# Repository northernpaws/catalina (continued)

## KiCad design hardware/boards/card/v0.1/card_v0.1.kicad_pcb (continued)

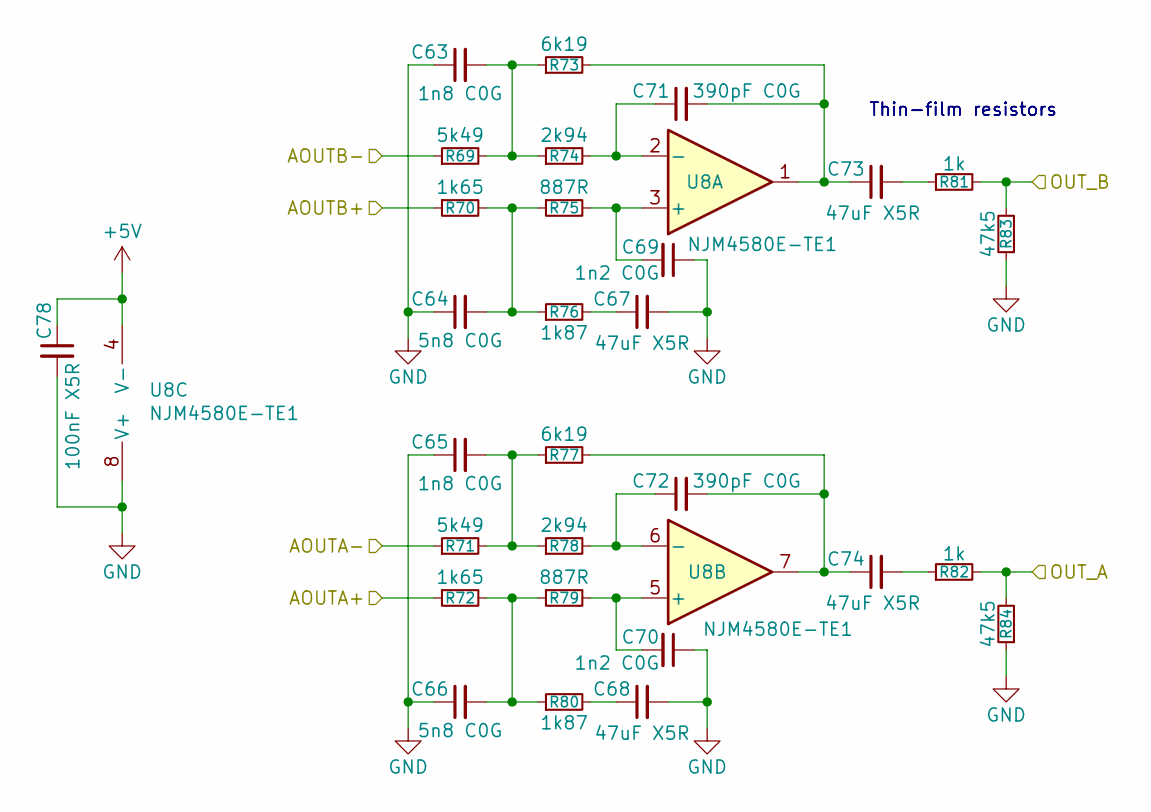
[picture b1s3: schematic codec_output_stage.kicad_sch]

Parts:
C63, C65: 1n8 C0G; C0402
C64, C66: 5n8 C0G; C0402
C67, C68, C73, C74: 47uF X5R; C0805
C69, C70: 1n2 C0G; C0402
C71, C72: 390pF C0G; C0402
C78: 100nF X5R; C0402
R69, R71: 5k49; R0402
R70, R72: 1k65; R0402
R73, R77: 6k19; R0402
R74, R78: 2k94; R0402
R75, R79: 887R; R0402
R76, R80: 1k87; R0402
R81, R82: 1k; R0402
R83, R84: 47k5; R0402
U8: NJM4580E-TE1; TSSOP-8_3x3mm_P0.65mm

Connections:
+5V: C78.1, U8.4 (V-); also elsewhere on the board
/Audio Codec/AOUTA1+: R72.1; also elsewhere on the board
/Audio Codec/AOUTA1-: R71.1; also elsewhere on the board
/Audio Codec/AOUTB1+: R70.1; also elsewhere on the board
/Audio Codec/AOUTB1-: R69.1; also elsewhere on the board
/Audio Codec/OUT_A1: R82.2, R84.2; also elsewhere on the board
/Audio Codec/OUT_B1: R81.2, R83.2; also elsewhere on the board
GND: C63.1, C64.1, C65.1, C66.1, C67.2, C68.2, C69.1, C70.1, C78.2, R83.1, R84.1, U8.8 (V+); also elsewhere on the board
unnamed: C63.2, R69.2, R73.1, R74.1
unnamed: C64.2, R70.2, R75.1, R76.1
unnamed: C65.2, R71.2, R77.1, R78.1
unnamed: C66.2, R72.2, R79.1, R80.1
unnamed: C67.1, R76.2
unnamed: C68.1, R80.2
unnamed: C71.2, C73.1, R73.2, U8.1
unnamed: C72.2, C74.1, R77.2, U8.7
unnamed: C73.2, R81.1
unnamed: C74.2, R82.1
unnamed: C69.2, R75.2, U8.3 (+)
unnamed: C71.1, R74.2, U8.2 (-)
unnamed: C70.2, R79.2, U8.5 (+)
unnamed: C72.1, R78.2, U8.6 (-)

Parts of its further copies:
C18, C33, C39, C41, C51, C53: 1n8 C0G; C0402
C19, C34, C40, C42, C52, C54: 5n8 C0G; C0402
C24, C37, C47, C48, C59, C60: 390pF C0G; C0402
C30, C32, C35, C38, C43, C44, C49, C50, C55, C56, C61, C62: 47uF X5R; C0805
C31, C36, C45, C46, C57, C58: 1n2 C0G; C0402
C75, C76, C77: 100nF X5R; C0402
R21, R32, R42, R46, R58, R62: 2k94; R0402
R22, R29, R37, R39, R53, R55: 5k49; R0402
R23, R30, R38, R40, R54, R56: 1k65; R0402
R24, R33, R43, R47, R59, R63: 887R; R0402
R25, R31, R41, R45, R57, R61: 6k19; R0402
R26, R34, R44, R48, R60, R64: 1k87; R0402
R27, R35, R49, R50, R65, R66: 1k; R0402
R28, R36, R51, R52, R67, R68: 47k5; R0402
U5, U6, U7: NJM4580E-TE1; TSSOP-8_3x3mm_P0.65mm

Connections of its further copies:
+5V: C75.1, C76.1, C77.1, U5.4 (V-), U6.4 (V-), U7.4 (V-); also elsewhere on the board
/Audio Codec/AOUTA2+: R56.1; also elsewhere on the board
/Audio Codec/AOUTA2-: R55.1; also elsewhere on the board
/Audio Codec/AOUTA3+: R40.1; also elsewhere on the board
/Audio Codec/AOUTA3-: R39.1; also elsewhere on the board
/Audio Codec/AOUTA4+: R30.1; also elsewhere on the board
/Audio Codec/AOUTA4-: R29.1; also elsewhere on the board
/Audio Codec/AOUTB2+: R54.1; also elsewhere on the board
/Audio Codec/AOUTB2-: R53.1; also elsewhere on the board
/Audio Codec/AOUTB3+: R38.1; also elsewhere on the board
/Audio Codec/AOUTB3-: R37.1; also elsewhere on the board
/Audio Codec/AOUTB4+: R23.1; also elsewhere on the board
/Audio Codec/AOUTB4-: R22.1; also elsewhere on the board
/Audio Codec/OUT_A2: R66.2, R68.2; also elsewhere on the board
/Audio Codec/OUT_A3: R50.2, R52.2; also elsewhere on the board
/Audio Codec/OUT_A4: R35.2, R36.2; also elsewhere on the board
/Audio Codec/OUT_B2: R65.2, R67.2; also elsewhere on the board
/Audio Codec/OUT_B3: R49.2, R51.2; also elsewhere on the board
/Audio Codec/OUT_B4: R27.2, R28.2; also elsewhere on the board
GND: C18.1, C19.1, C30.2, C31.1, C33.1, C34.1, C35.2, C36.1, C39.1, C40.1, C41.1, C42.1, C43.2, C44.2, C45.1, C46.1, C51.1, C52.1, C53.1, C54.1, C55.2, C56.2, C57.1, C58.1, C75.2, C76.2, C77.2, R28.1, R36.1, R51.1, R52.1, R67.1, R68.1, U5.8 (V+), U6.8 (V+), U7.8 (V+); also elsewhere on the board
unnamed: C18.2, R21.1, R22.2, R25.1
unnamed: C19.2, R23.2, R24.1, R26.1
unnamed: C24.2, C32.1, R25.2, U5.1
unnamed: C30.1, R26.2
unnamed: C32.2, R27.1
unnamed: C33.2, R29.2, R31.1, R32.1
unnamed: C34.2, R30.2, R33.1, R34.1
unnamed: C35.1, R34.2
unnamed: C37.2, C38.1, R31.2, U5.7
unnamed: C38.2, R35.1
unnamed: C39.2, R37.2, R41.1, R42.1
unnamed: C40.2, R38.2, R43.1, R44.1
unnamed: C41.2, R39.2, R45.1, R46.1
unnamed: C42.2, R40.2, R47.1, R48.1
unnamed: C43.1, R44.2
unnamed: C44.1, R48.2
unnamed: C47.2, C49.1, R41.2, U6.1
unnamed: C48.2, C50.1, R45.2, U6.7
unnamed: C49.2, R49.1
unnamed: C50.2, R50.1
unnamed: C51.2, R53.2, R57.1, R58.1
unnamed: C52.2, R54.2, R59.1, R60.1
unnamed: C53.2, R55.2, R61.1, R62.1
unnamed: C54.2, R56.2, R63.1, R64.1
unnamed: C55.1, R60.2
unnamed: C56.1, R64.2
unnamed: C59.2, C61.1, R57.2, U7.1
unnamed: C60.2, C62.1, R61.2, U7.7
unnamed: C61.2, R65.1
unnamed: C62.2, R66.1
unnamed: C31.2, R24.2, U5.3 (+)
unnamed: C24.1, R21.2, U5.2 (-)
unnamed: C36.2, R33.2, U5.5 (+)
unnamed: C37.1, R32.2, U5.6 (-)
unnamed: C45.2, R43.2, U6.3 (+)
unnamed: C47.1, R42.2, U6.2 (-)
unnamed: C46.2, R47.2, U6.5 (+)
unnamed: C48.1, R46.2, U6.6 (-)
unnamed: C57.2, R59.2, U7.3 (+)
unnamed: C59.1, R58.2, U7.2 (-)
unnamed: C58.2, R63.2, U7.5 (+)
unnamed: C60.1, R62.2, U7.6 (-)

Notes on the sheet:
Thin-film resistors

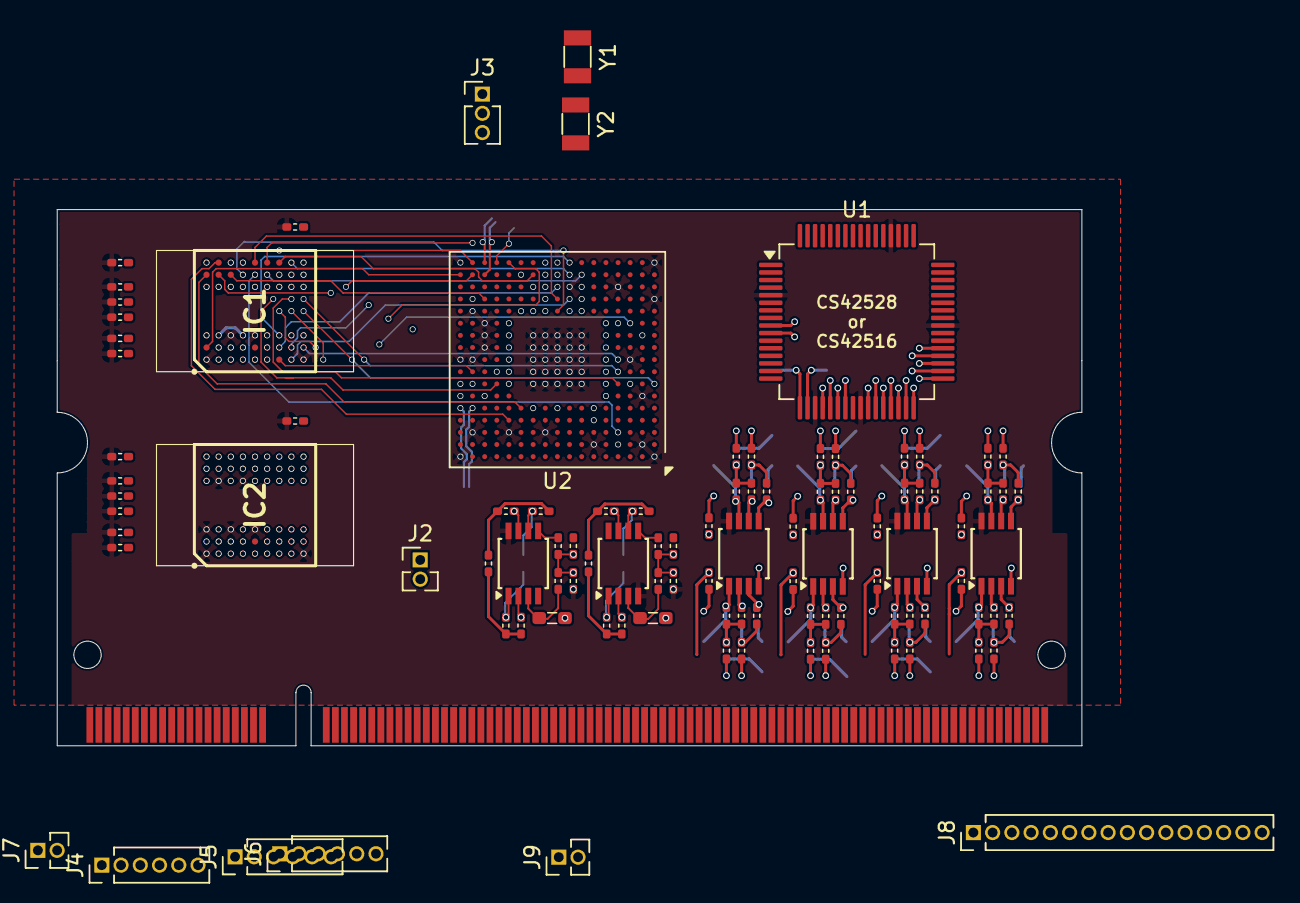
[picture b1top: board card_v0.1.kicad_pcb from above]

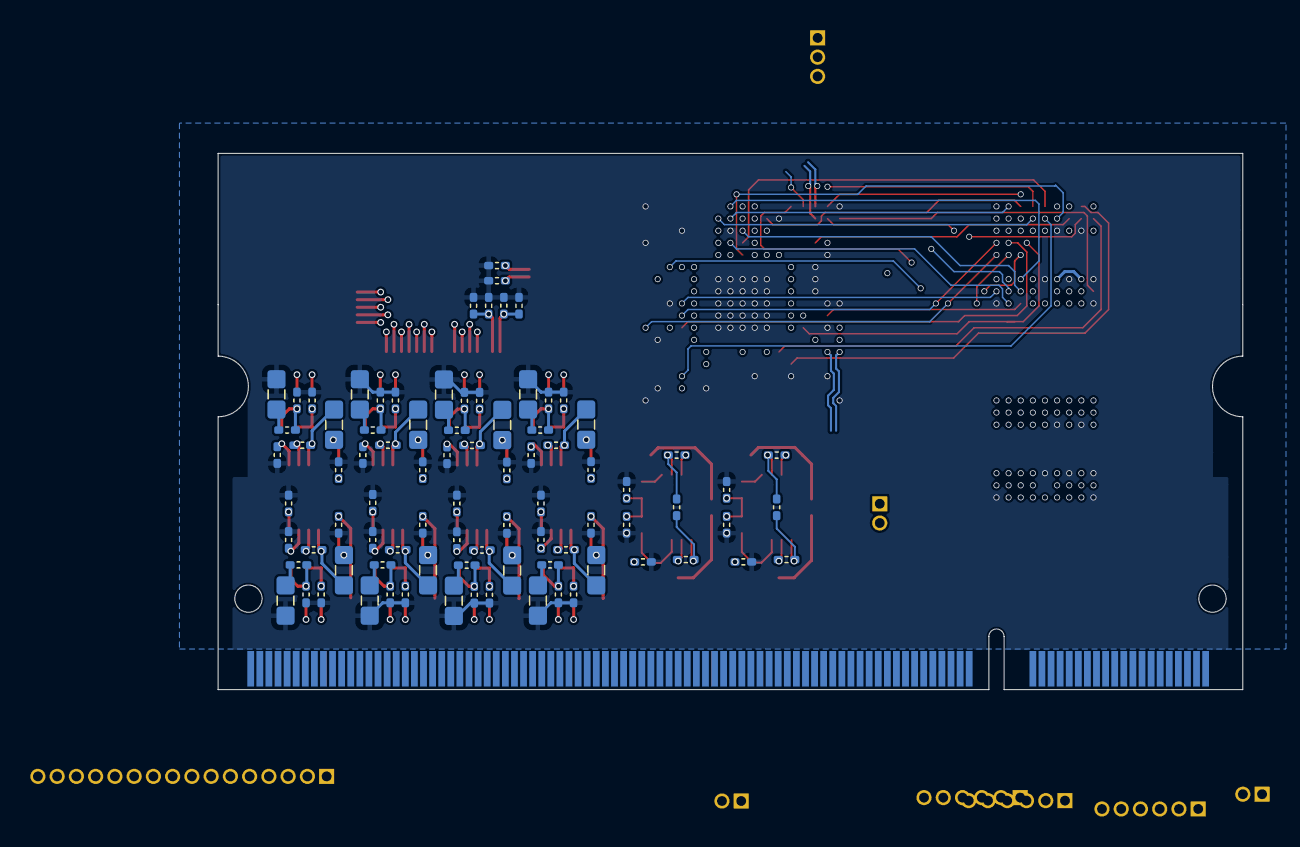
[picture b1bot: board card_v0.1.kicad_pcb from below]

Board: 6 copper layers, 67.6 x 35.4 mm, 189 parts (86 on the bottom side), 172 nets.

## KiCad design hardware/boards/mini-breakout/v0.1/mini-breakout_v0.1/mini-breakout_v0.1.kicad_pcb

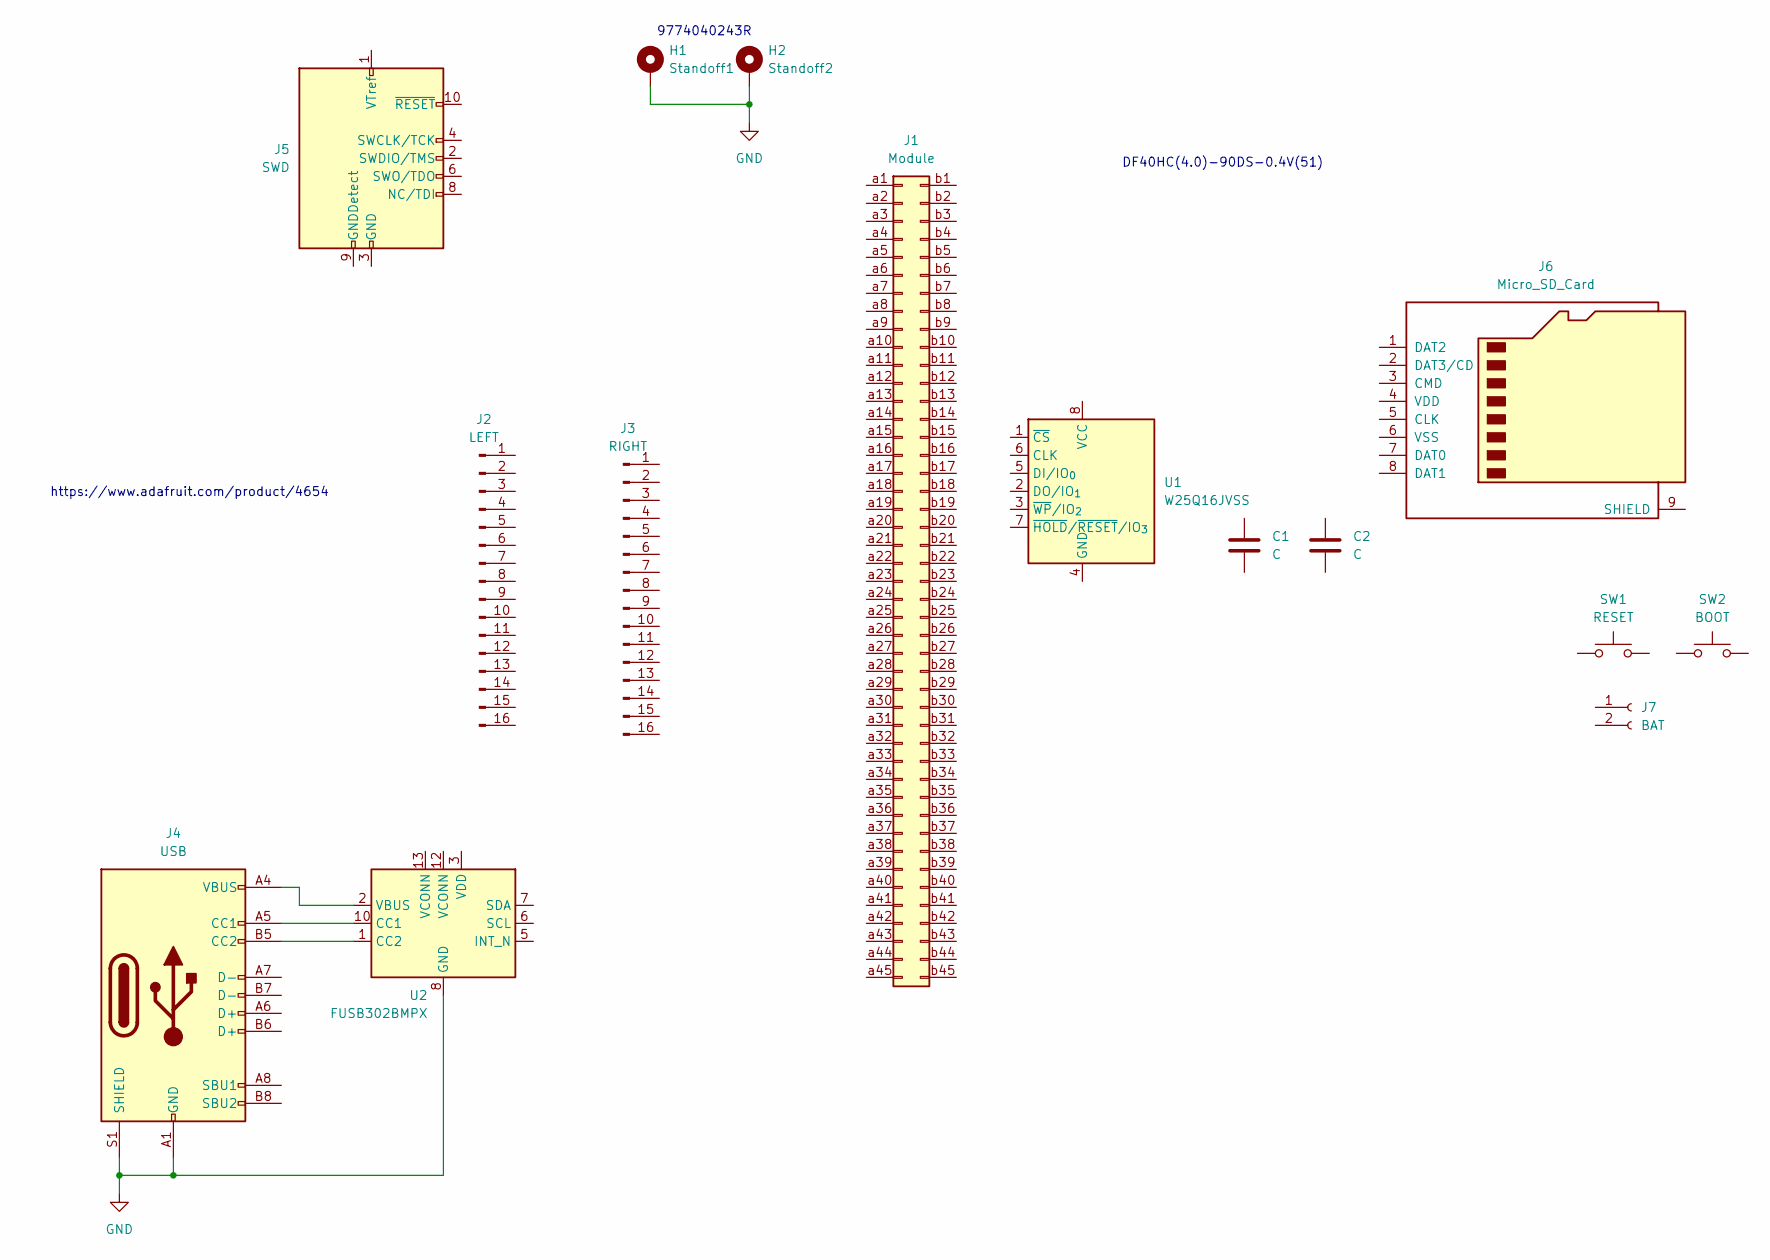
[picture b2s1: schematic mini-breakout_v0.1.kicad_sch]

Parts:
C1, C2: C; CP_Elec_5x5.9
H1: Standoff1; WA-SMSI_9774040243
H2: Standoff2; WA-SMSI_9774040243
J1: Module; Mini-v0.3
J2: LEFT; PinHeader_1x16_P2.54mm_Vertical
J3: RIGHT; PinHeader_1x16_P2.54mm_Vertical
J4: USB; USB_C_Receptacle_HCTL_HC-TYPE-C-16P-01A
J5: SWD; PinHeader_2x05_P1.27mm_Vertical_SMD
J6: Micro_SD_Card; microSD_HC_Molex_47219-2001
J7: BAT; JST_PH_S2B-PH-SM4-TB_1x02-1MP_P2.00mm_Horizontal
SW1: RESET; SW_Push_SPST_NO_Alps_SKRK
SW2: BOOT; SW_Push_SPST_NO_Alps_SKRK
U1: W25Q16JVSS; SOIC-8_5.3x5.3mm_P1.27mm
U2: FUSB302BMPX; WQFN-14-1EP_2.5x2.5mm_P0.5mm_EP1.45x1.45mm

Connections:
GND: H1.1, H2.1, J4.A1 (GND), J4.A12 (GND), J4.B1 (GND), J4.B12 (GND), J4.S1 (SHIELD), U2.8 (GND), U2.9 (GND), U2.15 (GND)
unnamed: J4.A5 (CC1), U2.10 (CC1), U2.11 (CC1)
unnamed: J4.B5 (CC2), U2.1 (CC2), U2.14 (CC2)
unnamed: J5.3 (GND), J5.5 (GND)
unnamed: J4.A4 (VBUS), J4.A9 (VBUS), J4.B4 (VBUS), J4.B9 (VBUS), U2.2 (VBUS)
unnamed: U2.3 (VDD), U2.4 (VDD)

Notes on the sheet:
https://www.adafruit.com/product/4654
DF40HC(4.0)-90DS-0.4V(51)
9774040243R

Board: 4 copper layers, 15 parts (2 on the bottom side), 6 nets, no tracks yet.

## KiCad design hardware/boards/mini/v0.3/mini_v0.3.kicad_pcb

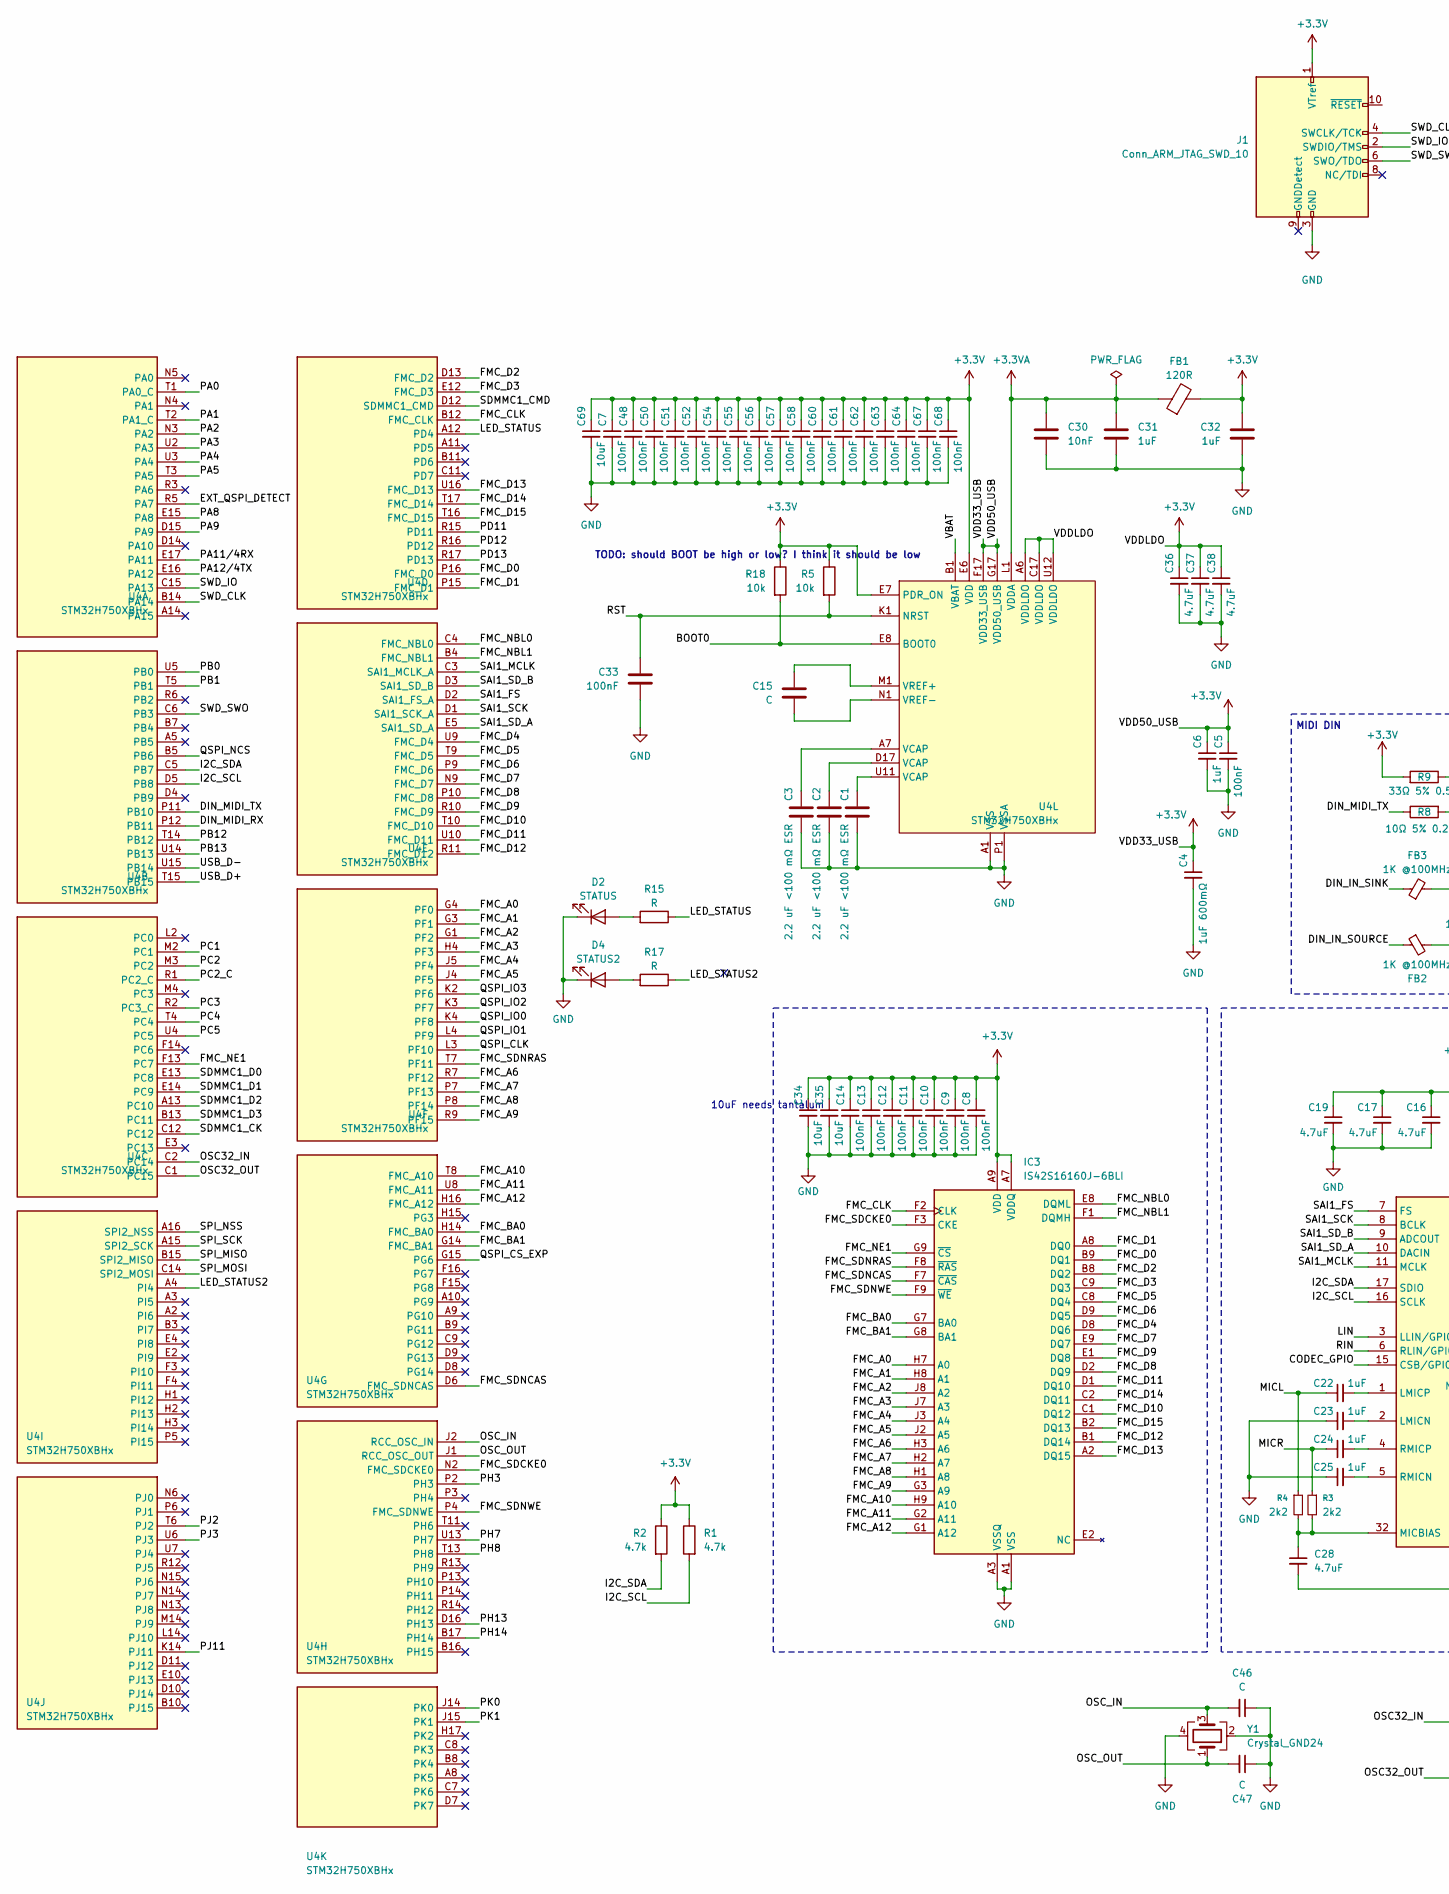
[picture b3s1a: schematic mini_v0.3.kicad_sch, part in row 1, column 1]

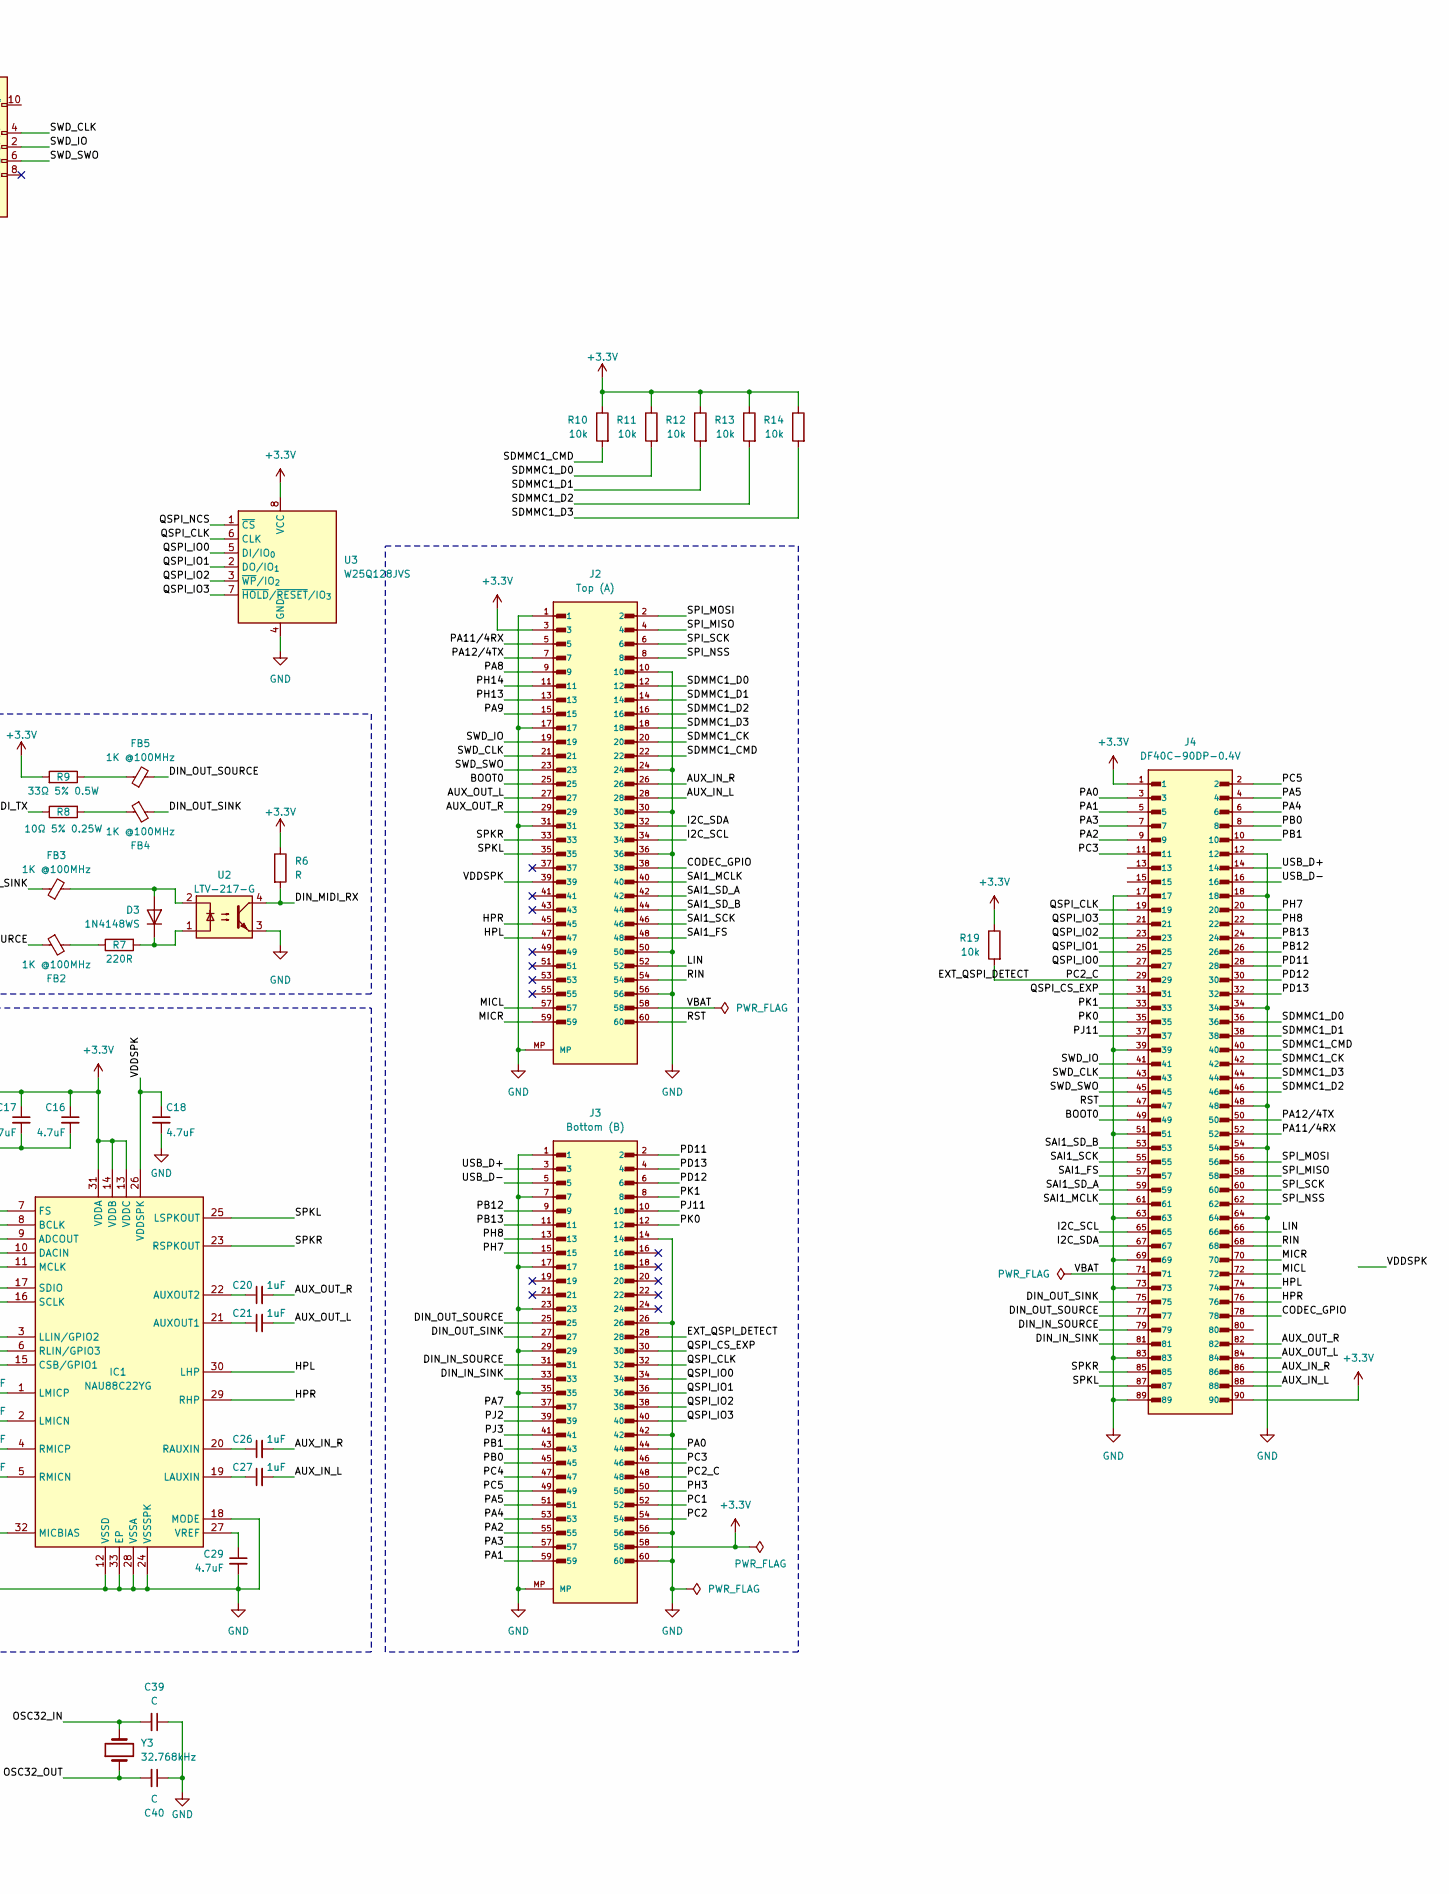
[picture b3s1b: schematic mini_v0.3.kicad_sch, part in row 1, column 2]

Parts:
C1, C2, C3: 2.2 uF <100 mΩ ESR; C_0402_1005Metric; LCSC C170151
C4: 1uF 600mΩ; C_0402_1005Metric; LCSC C14445
C5, C7, C8, C9, C10, C11, C12, C13, C14, C33, C48, C50, C51, C52, C54, C55, C56, C57, C58, C60, C61, C62, C63, C64, C67, C68: 100nF; C_0402_1005Metric; LCSC C3015120
C6, C20, C21, C22, C23, C24, C25, C26, C27, C31, C32: 1uF; C_0402_1005Metric; LCSC C3833440
C15, C39, C40, C46, C47: C; C_0402_1005Metric
C16, C17, C18, C19, C28, C29, C36, C37, C38: 4.7uF; C_0402_1005Metric; LCSC C2986065
C30: 10nF; C_0402_1005Metric; LCSC C1852256
C34, C35, C69: 10uF; C_0402_1005Metric; LCSC C315248
D2: STATUS; LED_0603_1608Metric
D3: 1N4148WS; D_SOD-323
D4: STATUS2; LED_0603_1608Metric
FB1: 120R; L_0402_1005Metric; LCSC C76891
FB2, FB3, FB4, FB5: 1K @100MHz; L_0402_1005Metric; LCSC C76889
IC1: NAU88C22YG; QFN-32-1EP_5x5mm_P0.5mm_EP3.6x3.6mm; Mouser Part Number 503-NAU88C22YG
IC3: IS42S16160J-6BLI; Alliance_TFBGA-54_8x8mm_Layout9x9_P0.8mm; Manufacturer_Part_Number IS42S16160J-6BLI; Mouser Part Number 870-42S16160J6BLI
J1: Conn_ARM_JTAG_SWD_10; paw-3mm
J2: Top (A); Hirose_DF40C-60DP-0.4V_2x30-1MP_P0.4mm; PARTREV 8; LCSC C424647
J3: Bottom (B); Hirose_DF40C-60DP-0.4V_2x30-1MP_P0.4mm; PARTREV 8; LCSC C424647
J4: DF40C-90DP-0.4V; Hirose_DF40C-90DP-0.4V_2x45-1MP_P0.4mm; PARTREV 8; DigiKey_Part_Number H11614CT-ND
R1, R2: 4.7k; R_0402_1005Metric; LCSC C105871
R3, R4: 2k2; R_0402_1005Metric; LCSC C114762
R5, R10, R11, R12, R13, R14, R18, R19: 10k; R_0402_1005Metric; LCSC C60490
R6, R15, R17: R; R_0402_1005Metric
R7: 220R; R_0402_1005Metric; LCSC C112291
R8: 10Ω 5% 0.25W; R_0402_1005Metric
R9: 33Ω 5% 0.5W; R_0402_1005Metric
U2: LTV-217-G; SOIC-4_4.55x2.6mm_P1.27mm; LCSC C17407902
U3: W25Q128JVS; SOIC-8_5.3x5.3mm_P1.27mm
U4: STM32H750XBHx; TFBGA-265_14x14mm_Layout17x17_P0.8mm; LCSC C405932
Y1: Crystal_GND24; Crystal_SMD_Abracon_ABM10-4Pin_2.5x2.0mm
Y3: 32.768kHz; Crystal_SMD_3215-2Pin_3.2x1.5mm; LCSC C32346

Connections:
+3.3V: C4.1, C5.1, C6.1, C7.1, C8.1, C9.1, C10.1, C11.1, C12.1, C13.1, C14.1, C16.1, C17.1, C19.1, C32.1, C34.1, C35.1, C36.1, C37.1, C38.1, C48.1, C50.1, C51.1, C52.1, C54.1, C55.1, C56.1, C57.1, C58.1, C60.1, C61.1, C62.1, C63.1, C64.1, C67.1, C68.1, C69.1, FB1.2, IC1.13 (VDDC), IC1.14 (VDDB), IC1.31 (VDDA), IC3.A7 (VDDQ), IC3.A9 (VDD), IC3.B3 (VDDQ), IC3.C7 (VDDQ), IC3.D3 (VDDQ), IC3.E7 (VDD), IC3.J9 (VDD), J1.1 (VTref), J2.3, J3.58, J4.1, J4.90, R1.1, R2.1, R5.1, R6.1, R9.2, R10.1, R11.1, R12.1, R13.1, R14.1, R18.1, R19.1, U3.8 (VCC), U4.A6 (VDDLDO), U4.C17 (VDDLDO), U4.E6 (VDD), U4.E7 (PDR_ON), U4.E9 (VDD), U4.E11 (VDD), U4.F5 (VDD), U4.F17 (VDD33_USB), U4.G5 (VDD), U4.G13 (VDD), U4.G17 (VDD50_USB), U4.H5 (VDD), U4.H13 (VDD), U4.J13 (VDD), U4.K5 (VDD), U4.K13 (VDD), U4.L5 (VDD), U4.L13 (VDD), U4.M5 (VDD), U4.M13 (VDD), U4.N7 (VDD), U4.N8 (VDD), U4.N10 (VDD), U4.N11 (VDD), U4.N12 (VDD), U4.P17 (VDD), U4.U12 (VDDLDO)
+3.3VA: C30.1, C31.1, FB1.1, U4.L1 (VDDA)
/AUX_IN_L: C27.2, J2.28, J4.88
/AUX_IN_R: C26.2, J2.26, J4.86
/AUX_OUT_L: C21.2, J2.27, J4.84
/AUX_OUT_R: C20.2, J2.29, J4.82
/BOOT0: J2.25, J4.49, R18.2, U4.E8 (BOOT0)
/CODEC_GPIO: IC1.15 (CSB/GPIO1), J2.38, J4.78
/DIN_IN_SINK: FB3.1, J3.33, J4.81
/DIN_IN_SOURCE: FB2.1, J3.31, J4.79
/DIN_MIDI_RX: R6.2, U2.4, U4.P12 (PB11)
/DIN_MIDI_TX: R8.1, U4.P11 (PB10)
/DIN_OUT_SINK: FB4.2, J3.27, J4.75
/DIN_OUT_SOURCE: FB5.2, J3.25, J4.77
/EXT_QSPI_DETECT: J3.28, J3.48, J4.29, R19.2, U4.R1 (PC2_C), U4.R5 (PA7)
/FMC_A0: IC3.H7 (A0), U4.G4 (PF0)
/FMC_A1: IC3.H8 (A1), U4.G3 (PF1)
/FMC_A2: IC3.J8 (A2), U4.G1 (PF2)
/FMC_A3: IC3.J7 (A3), U4.H4 (PF3)
/FMC_A4: IC3.J3 (A4), U4.J5 (PF4)
/FMC_A5: IC3.J2 (A5), U4.J4 (PF5)
/FMC_A6: IC3.H3 (A6), U4.R7 (PF12)
/FMC_A7: IC3.H2 (A7), U4.P7 (PF13)
/FMC_A8: IC3.H1 (A8), U4.P8 (PF14)
/FMC_A9: IC3.G3 (A9), U4.R9 (PF15)
/FMC_A10: IC3.H9 (A10), U4.T8 (FMC_A10)
/FMC_A11: IC3.G2 (A11), U4.U8 (FMC_A11)
/FMC_A12: IC3.G1 (A12), U4.H16 (FMC_A12)
/FMC_BA0: IC3.G7 (BA0), U4.H14 (FMC_BA0)
/FMC_BA1: IC3.G8 (BA1), U4.G14 (FMC_BA1)
/FMC_CLK: IC3.F2 (CLK), U4.B12 (FMC_CLK)
/FMC_D0: IC3.B9 (DQ1), U4.P16 (FMC_D0)
/FMC_D1: IC3.A8 (DQ0), U4.P15 (FMC_D1)
/FMC_D2: IC3.B8 (DQ2), U4.D13 (FMC_D2)
/FMC_D3: IC3.C9 (DQ3), U4.E12 (FMC_D3)
/FMC_D4: IC3.D8 (DQ6), U4.U9 (FMC_D4)
/FMC_D5: IC3.C8 (DQ4), U4.T9 (FMC_D5)
/FMC_D6: IC3.D9 (DQ5), U4.P9 (FMC_D6)
/FMC_D7: IC3.E9 (DQ7), U4.N9 (FMC_D7)
/FMC_D8: IC3.D2 (DQ9), U4.P10 (FMC_D8)
/FMC_D9: IC3.E1 (DQ8), U4.R10 (FMC_D9)
/FMC_D10: IC3.C1 (DQ12), U4.T10 (FMC_D10)
/FMC_D11: IC3.D1 (DQ10), U4.U10 (FMC_D11)
/FMC_D12: IC3.B1 (DQ14), U4.R11 (FMC_D12)
/FMC_D13: IC3.A2 (DQ15), U4.U16 (FMC_D13)
/FMC_D14: IC3.C2 (DQ11), U4.T17 (FMC_D14)
/FMC_D15: IC3.B2 (DQ13), U4.T16 (FMC_D15)
/FMC_NBL0: IC3.E8 (DQML), U4.C4 (FMC_NBL0)
/FMC_NBL1: IC3.F1 (DQMH), U4.B4 (FMC_NBL1)
/FMC_NE1: IC3.G9 (~CS), U4.F13 (PC7)
/FMC_SDCKE0: IC3.F3 (CKE), U4.N2 (FMC_SDCKE0)
/FMC_SDNCAS: IC3.F7 (~CAS), U4.D6 (FMC_SDNCAS)
/FMC_SDNRAS: IC3.F8 (~RAS), U4.T7 (PF11)
/FMC_SDNWE: IC3.F9 (~WE), U4.P4 (FMC_SDNWE)
/HPL: IC1.30 (LHP), J2.47, J4.74
/HPR: IC1.29 (RHP), J2.45, J4.76
/I2C_SCL: IC1.16 (SCLK), J2.34, J4.65, R1.2, U4.D5 (PB8)
/I2C_SDA: IC1.17 (SDIO), J2.32, J4.67, R2.2, U4.C5 (PB7)
/LED_STATUS: R15.1, U4.A12 (PD4)
/LED_STATUS2: R17.1, U4.A4 (PI4)
/LIN: IC1.3 (LLIN/GPIO2), J2.52, J4.66
/MICL: C22.1, J2.57, J4.72, R4.1
/MICR: C24.1, J2.59, J4.70, R3.1
/OSC32_IN: C39.2, U4.C2 (PC14), Y3.2
/OSC32_OUT: C40.2, U4.C1 (PC15), Y3.1
/OSC_IN: C46.2, U4.J2 (RCC_OSC_IN), Y1.3
/OSC_OUT: C47.2, U4.J1 (RCC_OSC_OUT), Y1.1
/PA0: J3.44, J4.3, U4.T1 (PA0_C)
/PA1: J3.59, J4.5, U4.T2 (PA1_C)
/PA2: J3.55, J4.9, U4.N3 (PA2)
/PA3: J3.57, J4.7, U4.U2 (PA3)
/PA4: J3.53, J4.6, U4.U3 (PA4)
/PA5: J3.51, J4.4, U4.T3 (PA5)
/PA8: J2.9, U4.E15 (PA8)
/PA9: J2.15, U4.D15 (PA9)
/PA11/4RX: J2.5, J4.52, U4.E17 (PA11)
/PA12/4TX: J2.7, J4.50, U4.E16 (PA12)
/PB0: J3.45, J4.8, U4.U5 (PB0)
/PB1: J3.43, J4.10, U4.T5 (PB1)
/PB12: J3.9, J4.26, U4.T14 (PB12)
/PB13: J3.11, J4.24, U4.U14 (PB13)
/PC1: J3.52, U4.M2 (PC1)
/PC2: J3.54, U4.M3 (PC2)
/PC3: J3.46, J4.11, U4.R2 (PC3_C)
/PC4: J3.47, U4.T4 (PC4)
/PC5: J3.49, J4.2, U4.U4 (PC5)
/PD11: J3.2, J4.28, U4.R15 (PD11)
/PD12: J3.6, J4.30, U4.R16 (PD12)
/PD13: J3.4, J4.32, U4.R17 (PD13)
/PH3: J3.50, U4.P2 (PH3)
/PH7: J3.15, J4.20, U4.U13 (PH7)
/PH8: J3.13, J4.22, U4.T13 (PH8)
/PH13: J2.13, U4.D16 (PH13)
/PH14: J2.11, U4.B17 (PH14)
/PJ2: J3.39, U4.T6 (PJ2)
/PJ3: J3.41, U4.U6 (PJ3)
/PJ11: J3.10, J4.37, U4.K14 (PJ11)
/PK0: J3.12, J4.35, U4.J14 (PK0)
/PK1: J3.8, J4.33, U4.J15 (PK1)
/QSPI_CLK: J3.32, J4.19, U3.6 (CLK), U4.L3 (PF10)
/QSPI_CS_EXP: J3.30, J4.31, U4.G15 (PG6)
/QSPI_IO0: J3.34, J4.27, U3.5 (DI/IO_{0}), U4.K4 (PF8)
/QSPI_IO1: J3.36, J4.25, U3.2 (DO/IO_{1}), U4.L4 (PF9)
/QSPI_IO2: J3.38, J4.23, U3.3 (~WP/IO_{2}), U4.K3 (PF7)
/QSPI_IO3: J3.40, J4.21, U3.7 (~HOLD/~RESET/IO_{3}), U4.K2 (PF6)
/QSPI_NCS: U3.1 (~CS), U4.B5 (PB6)
/RIN: IC1.6 (RLIN/GPIO3), J2.54, J4.68
/RST: C33.1, J2.60, J4.47, R5.2, U4.K1 (NRST)
/SAI1_FS: IC1.7 (FS), J2.48, J4.57, U4.D2 (SAI1_FS_A)
/SAI1_MCLK: IC1.11 (MCLK), J2.40, J4.61, U4.C3 (SAI1_MCLK_A)
/SAI1_SCK: IC1.8 (BCLK), J2.46, J4.55, U4.D1 (SAI1_SCK_A)
/SAI1_SD_A: IC1.10 (DACIN), J2.42, J4.59, U4.E5 (SAI1_SD_A)
/SAI1_SD_B: IC1.9 (ADCOUT), J2.44, J4.53, U4.D3 (SAI1_SD_B)
/SDMMC1_CK: J2.20, J4.42, U4.C12
/SDMMC1_CMD: J2.22, J4.40, R10.2, U4.D12 (SDMMC1_CMD)
/SDMMC1_D0: J2.12, J4.36, R11.2, U4.E13 (PC8)
/SDMMC1_D1: J2.14, J4.38, R12.2, U4.E14 (PC9)
/SDMMC1_D2: J2.16, J4.46, R13.2, U4.A13 (PC10)
/SDMMC1_D3: J2.18, J4.44, R14.2, U4.B13 (PC11)
/SPI_MISO: J2.4, J4.58, U4.B15 (SPI2_MISO)
/SPI_MOSI: J2.2, J4.56, U4.C14 (SPI2_MOSI)
/SPI_NSS: J2.8, J4.62, U4.A16 (SPI2_NSS)
/SPI_SCK: J2.6, J4.60, U4.A15 (SPI2_SCK)
/SPKL: IC1.25 (LSPKOUT), J2.35, J4.87
/SPKR: IC1.23 (RSPKOUT), J2.33, J4.85
/SWD_CLK: J1.4 (SWCLK/TCK), J2.21, J4.43, U4.B14 (PA14)
/SWD_IO: J1.2 (SWDIO/TMS), J2.19, J4.41, U4.C15 (PA13)
/SWD_SWO: J1.6 (SWO/TDO), J2.23, J4.45, U4.C6 (PB3)
/USB_D+: J3.3, J4.14, U4.T15 (PB15)
/USB_D-: J3.5, J4.16, U4.U15 (PB14)
/VBAT: J2.58, J4.71, U4.B1 (VBAT)
/VDDSPK: C18.1, IC1.26 (VDDSPK), J2.39
GND: C1.2, C2.2, C3.2, C4.2, C5.2, C6.2, C7.2, C8.2, C9.2, C10.2, C11.2, C12.2, C13.2, C14.2, C16.2, C17.2, C18.2, C19.2, C23.1, C25.1, C28.2, C29.2, C30.2, C31.2, C32.2, C33.2, C34.2, C35.2, C36.2, C37.2, C38.2, C39.1, C40.1, C46.1, C47.1, C48.2, C50.2, C51.2, C52.2, C54.2, C55.2, C56.2, C57.2, C58.2, C60.2, C61.2, C62.2, C63.2, C64.2, C67.2, C68.2, C69.2, D2.1 (K), D4.1 (K), IC1.12 (VSSD), IC1.18 (MODE), IC1.24 (VSSSPK), IC1.28 (VSSA), IC1.33 (EP), IC3.A1 (VSS), IC3.A3 (VSSQ), IC3.B7 (VSSQ), IC3.C3 (VSSQ), IC3.D7 (VSSQ), IC3.E3 (VSS), IC3.J1 (VSS), J1.3 (GND), J1.5 (GND), J2.1, J2.10, J2.17, J2.24, J2.30, J2.31, J2.36, J2.50, J2.56, J2.MP, J3.1, J3.7, J3.14, J3.17, J3.23, J3.26, J3.29, J3.35, J3.42, J3.56, J3.60, J3.MP, J4.12, J4.17, J4.18, J4.34, J4.39, J4.48, J4.51, J4.54, J4.63, J4.64, J4.69, J4.73, J4.83, J4.89, U2.3, U3.4 (GND), U4.A1 (VSS), U4.A17 (VSS), U4.B2 (VSS), U4.B6 (VSS), U4.C10 (VSS), U4.C13 (VSS), U4.C16 (VSS), U4.F1 (VSS), U4.F2 (VSS), U4.G2 (VSS), U4.G7 (VSS), U4.G8 (VSS), U4.G9 (VSS), U4.G10 (VSS), U4.G11 (VSS), U4.G16 (VSS), U4.H7 (VSS), U4.H8 (VSS), U4.H9 (VSS), U4.H10 (VSS), U4.H11 (VSS), U4.J3 (VSS), U4.J7 (VSS), U4.J8 (VSS), U4.J9 (VSS), U4.J10 (VSS), U4.J11 (VSS), U4.J16 (VSS), U4.J17 (VSS), U4.K7 (VSS), U4.K8 (VSS), U4.K9 (VSS), U4.K10 (VSS), U4.K11 (VSS), U4.K15 (VSS), U4.L7 (VSS), U4.L8 (VSS), U4.L9 (VSS), U4.L10 (VSS), U4.L11 (VSS), U4.L15 (VSS), U4.M15 (VSS), U4.N16 (VSS), U4.P1 (VSSA), U4.R4 (VSS), U4.R8 (VSS), U4.T12 (VSS), U4.U1 (VSS), U4.U17 (VSS), Y1.2, Y1.4
unnamed: C1.1, U4.U11 (VCAP)
unnamed: C2.1, U4.D17 (VCAP)
unnamed: C3.1, U4.A7 (VCAP)
unnamed: D2.2 (A), R15.2
unnamed: D3.2 (A), FB3.2, U2.2
unnamed: D3.1 (K), R7.2, U2.1
unnamed: D4.2 (A), R17.2
unnamed: FB2.2, R7.1
unnamed: FB4.1, R8.2
unnamed: FB5.1, R9.1
unnamed: C21.1, IC1.21 (AUXOUT1)
unnamed: C20.1, IC1.22 (AUXOUT2)
unnamed: C27.1, IC1.19 (LAUXIN)
unnamed: C23.2, IC1.2 (LMICN)
unnamed: C22.2, IC1.1 (LMICP)
unnamed: C28.1, IC1.32 (MICBIAS), R3.2, R4.2
unnamed: C26.1, IC1.20 (RAUXIN)
unnamed: C25.2, IC1.5 (RMICN)
unnamed: C24.2, IC1.4 (RMICP)
unnamed: C29.1, IC1.27 (VREF)
unnamed: C15.1, U4.M1 (VREF+)
unnamed: C15.2, U4.N1 (VREF-)

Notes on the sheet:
TODO: should BOOT be high or low? I think it should be low
MIDI DIN
10uF needs tantalum

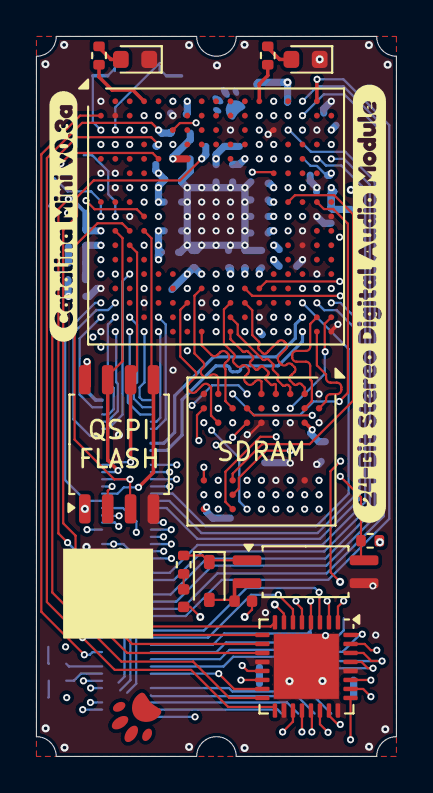
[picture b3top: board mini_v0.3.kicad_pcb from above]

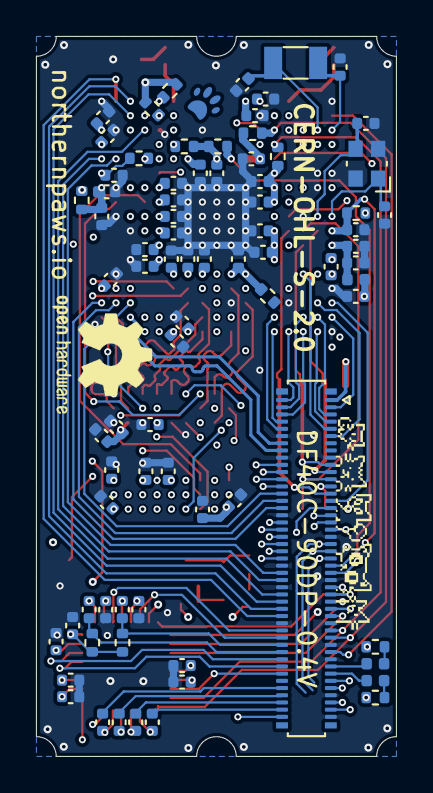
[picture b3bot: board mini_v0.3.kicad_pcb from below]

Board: 8 copper layers, 20.0 x 40.0 mm, 96 parts (79 on the bottom side), 145 nets.

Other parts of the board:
kibuzzard-69637FF5: G***; kibuzzard-69637FF5
kibuzzard-696388A5: G***; kibuzzard-696388A5

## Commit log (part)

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2025-12-01 start implementing engine sources and examples
2025-12-01 start adding audio traits and sine oscillator
2025-12-04 place stm32h750 decoupling capacitors
2025-12-04 mini: more SDRAM routing work
2025-12-04 second mini SDRAM routing attempt
2025-12-09 implement sine oscillator and example
2025-12-09 add live playback oscillator example
2025-12-09 use dasp-sample traits for sample typing
2025-12-10 wrap oscillator types into single struct
2025-12-10 implement lookup oscillator, use `dasp` crate instead of `dasp_sample` directly
2025-12-10 added README.md module documentation
2025-12-11 update `sine-synth` sample to new buffer format
2025-12-11 rename `theory` module to `music`
2025-12-11 fix note frequencies off by one octave
2025-12-11 revert octave fix based on incorrect frequency source
2025-12-11 add note steps in sine-synth example
2025-12-12 reorganize engine examples
2025-12-12 start adding `instruments` crate and additive synth example
2025-12-13 mini: change to x16 SDRAM
2025-12-13 mini: routed x16 SDRAM
2025-12-13 start adding embedded example
2025-12-14 mini: route codec, SDMMC, and MIDI in/out
2025-12-14 mini: route more GPIO
2025-12-14 mini: shorten bottom of board
2025-12-14 mini: more gpio routing
2025-12-15 add images of mini module to README.md
2025-12-15 mini: remove unused test points
2025-12-15 add link to mini schematic in README.md
2025-12-16 mini: start routing QSPI to lower connector
2025-12-16 mini: route external QSPI lines and LEDs
2025-12-16 mini: routing cleanup
2025-12-17 mini: added bites in PCB corners for mounting bolts
2025-12-17 mini: added LCSC BOM entries
2025-12-17 mini: length matching and skew routing
2025-12-19 mini: fix mounting bite sizing, make power input reversable without damage
2025-12-19 mini: start routing remaining lower GPIO
2025-12-20 add project licenses
2025-12-20 add current supporters to README.md
2025-12-20 add initial board support package crate
2025-12-20 add missing `no_std` flags
2025-12-20 mini: resolve ERC errors
2025-12-20 mini: start routing single connector layout
2025-12-21 mini: route SDMMC and SAI lines to near new connector
2025-12-21 mini: use 90-pin port instead of 80
2025-12-22 mini: various routing tweaks
2025-12-22 mini: various routing adjustments
2025-12-23 fix `core_intrinsics` error from `dasp`
2025-12-23 add missing version tags to workspace imports
2025-12-23 start adding cargo crate-specific README
2025-12-23 fix `dasp` using outdated release
2025-12-23 add descriptions to child crates
2025-12-23 inline crate docs for child crates
2025-12-23 update old references to `dasp` crate
2025-12-23 remove cargo `dasp` dependencies
2025-12-23 add crates.io link to README.md
2025-12-25 rename `Frequency` to `Hertz`
2025-12-25 port variable wave oscillator from Mutable Instrument's Plaits
2025-12-25 add attribution section to engine crate README.md
2025-12-25 port examples to new ocillator trait
2025-12-25 port `envelope:detect`, `peak`, `rms`, `interoplate`, `window`, and `ring_buffer` from dasp and remove `core_intrinsics` dependency
2025-12-25 add missing guards for `alloc` gated modules
2025-12-28 disable `serde` by default in engine
2025-12-28 move cli to seperate `catalina-cli` crate
2025-12-28 remove cli workflow
2025-12-28 add `no_std` feature for `float_eq`
2025-12-28 replace std intrinsics with libm for `no_std` compatibility without nightly toolchain
2025-12-31 fix oscillator phase over-running, leading to floating point math errors
2025-12-31 fix example playing triangle instead of sine
2025-12-31 add amplitude scaling to playback example
2026-01-01 update shadowed imports to improve `rust-analyser` discovery
2026-01-11 mini: various final DFM tweaks
2026-01-12 mini: re-route status LED, add paws, expose copper on screw points
2026-01-12 label examples in vscode workspace
2026-01-16 start mini breakout carrier board
2026-05-10 mini: add note about filter caps
2026-05-10 seq: start implementing step sequencer crate
2026-05-10 seq: add trigger condition logic and rough tests
2026-05-10 seq: add trigger defaults, add probability check
2026-05-10 machines: start adding machines crate
2026-05-10 seq: crate cleanup and reorganization
2026-05-11 seq: better define sequence timing, and document microtiming
2026-05-11 seq: remove extra microtiming type for clarity
